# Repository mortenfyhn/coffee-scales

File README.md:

# coffee-scales

Kitchen scales, built for drip coffee brewing:

* 0.1 gram precision
* Very quick response
* Very quick tare
* Auto-starting brew timer
* Auto-off after 5 minutes

Current prototype looks something like this:

## Firmware

Setup:

1. [Install PlatformIO Core and shell commands](https://docs.platformio.org/en/latest/core/installation/index.html)
2. [Install Just](https://just.systems/man/en/packages.html)

Usage:

```sh
cd firmware
just --list
```

to list all recipes.

## Hardware

* Adafruit Feather 328P
* Load cell: 1 kg straight bar
* HX711 load cell amplifier
* Two 4-digit 7-segment displays with TM1637 drivers
* LiPo battery (1200 mAh)
* Push button for taring

## Development and debugging

Capture a log with `just log`. Then run `just replay <log>` to get the processing stages as CSV, and look at them in e.g. PlotJuggler.

Here's the state diagram:

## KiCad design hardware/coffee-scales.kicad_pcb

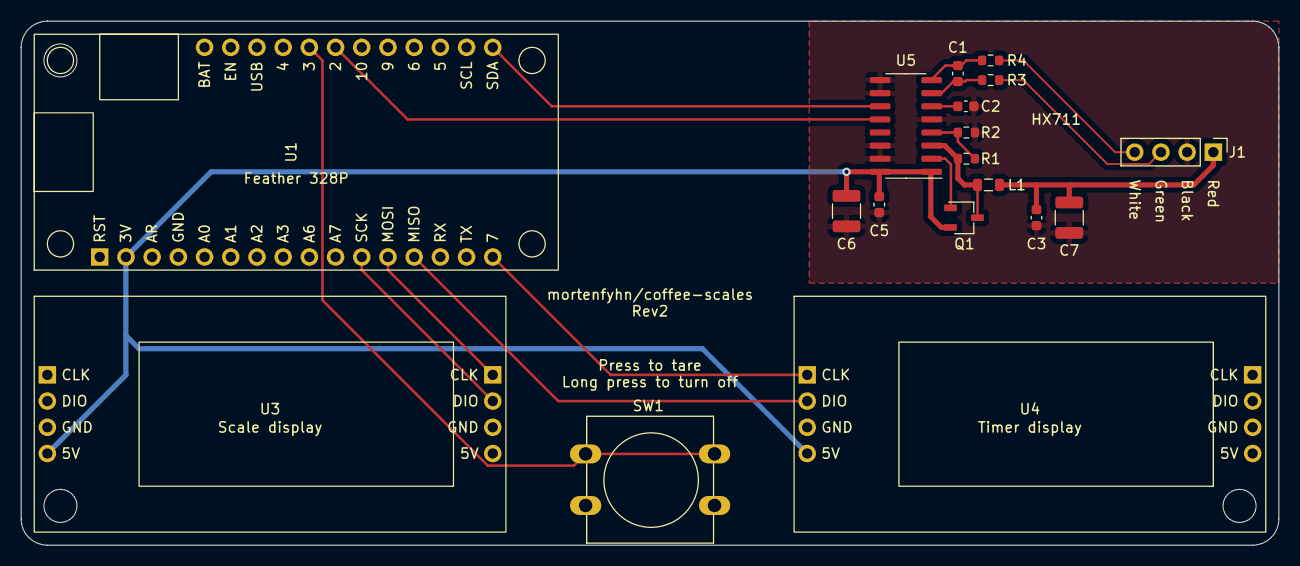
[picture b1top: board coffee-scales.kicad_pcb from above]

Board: 2 copper layers, 121.9 x 50.8 mm, 18 parts (0 on the bottom side), 18 nets.

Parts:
C1, C2, C3, C5: 0.1uF; C_0603_1608Metric
C6, C7: 10uF; C_1210_3225Metric
J1: Conn_01x04; PinHeader_1x04_P2.54mm_Vertical
L1: 3.3uH; L_0805_2012Metric
Q1: MMBT4403; TSOT-23
R1: 20k; R_0603_1608Metric
R2: 8.2k; R_0603_1608Metric
R3, R4: 100; R_0603_1608Metric
SW1: SW_Push; SW_PUSH-12mm
U1: Adafruit_Feather_328P
U3, U4: 4DIGIT_7SEG
U5: SOP-16_3.9x9.9mm_P1.27mm

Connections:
+3V3: C5.1, C6.1, Q1.2 (E), U1.2 (3V), U3.4 (5V), U4.4 (5V), U5.1 (VSUP), U5.16 (DVDD)
/HX711/A+: J1.4, R4.2
/HX711/A-: J1.3, R3.2
/HX711/DAT: U1.22 (D2), U5.12 (DOUT)
/HX711/E+: C3.1, C7.1, J1.1, L1.1
/HX711/SCK: U1.28 (SDA), U5.11 (PD_SCK)
GND: C2.1, C3.2, C5.2, C6.2, C7.2, J1.2, R2.2, SW1.2, U1.4 (GND), U3.3 (GND), U3.7 (GND), U4.3 (GND), U4.7 (GND), U5.5 (AGND), U5.9 (INNB), U5.10 (INPB), U5.14 (XI), U5.15 (RATE)
unnamed: Q1.1 (B), U5.2 (BASE)
unnamed: L1.2, Q1.3 (C), R1.1, U5.3 (AVDD)
unnamed: SW1.1, U1.21 (D3)
unnamed: U1.16 (D7), U4.1 (CLK)
unnamed: U1.13 (MISO), U4.2 (DIO)
unnamed: U1.12 (MOSI), U3.5 (CLK)
unnamed: U1.11 (SCK), U3.6 (DIO)
unnamed: C1.1, R3.1, U5.7 (INNA)
unnamed: C1.2, R4.1, U5.8 (INPA)
unnamed: C2.2, U5.6 (VBG)
unnamed: R1.2, R2.1, U5.4 (VFB)

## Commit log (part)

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2017-03-16 Add Arduino sketch
2017-08-29 Create object for gram display
2017-08-29 Create object for timer display
2017-08-29 Update pin numbers and load cell params
2017-08-29 Put opening braces on separate line
2017-08-29 Remove unnecessary filter initialization
2017-08-29 Clean up display classes
2017-09-14 Write a class for measurement filtering
2017-09-14 Tare on boot
2017-09-14 Implement hysteresis
    This reduces measurement jitter.
2017-09-14 Use member consts for smoothing filter parameters
2017-09-16 Add picture of scales to readme
2017-10-03 Remove needless functions from SmoothingFilter
2017-10-03 Take filter parameters in constructor
2017-10-03 Rename HX711 instance
2017-10-03 Un-align display instances
2017-10-03 Inherit SevenSegment classes
2017-10-03 Fix buffer size bug
    Super stupid, the extra element is needed for the decimal point.
    The _size member of RunningAverage happened to be after
    decigram_string in memory, and would get overwritten to zero,
    causing getStandardDeviation to return NAN.
2017-10-04 Update picture in readme
2017-10-04 Add support for negative weight
2017-10-10 Make static some functions that should be static
2018-07-20 Initialize platformio project
2018-07-20 Move sources to src/
2018-07-20 Rename coffee-scale.ino -> main.cpp
2018-07-20 Set monitor speed and library dependencies
2018-07-20 Add TM1637 library submodule
2018-07-20 Keep timer on
    Turns out it's really annoying that the timer resets when I remove the weight
    from the scales. Fixes #10.
2018-07-20 Set up .travis.yml
2018-07-20 Remove comment block from .travis.yml
2018-07-20 Add cool build status badge
2018-07-21 Add 500 ms delay on boot
    Fixes #11.
2018-07-21 Remove submodule stuff from travis config
2018-07-21 Add direct github link to lib_deps instead of submodule
2018-07-21 Fix constexpr warning
2019-06-01 Add build and run instructions to readme
2020-10-31 Update gitignore
2020-10-31 Update project config
2020-10-31 Update HX711 API calls
2020-11-01 Update lib README
2020-11-01 Use clang-format
2020-11-01 Remove submodule config
2020-11-01 Add Sublime Text project file
    Autogenerated from
    The current working directory /home/morten/workspace/coffee-scales will be used for the project.
    The next files/directories have been created in /home/morten/workspace/coffee-scales
    include - Put project header files here
    lib - Put here project specific (private) libraries
    src - Put project source files here
2020-11-01 Move project libs to lib/
2020-11-01 Fix warnings
2020-11-01 Setup GitHub Action
2020-11-01 Don't use SSH for dependencies
2020-11-01 Add build badge
2020-11-01 Set up scheduled build
2020-11-01 Update nightly build cron spec
    Fix #27.
2020-11-01 Refactor a bit
2020-11-01 Remove unnecessary parens
2020-11-01 Avoid printing -0.0
    Instead just print -0.1 as the first negative number.
2020-11-01 Improve tare accuracy
    Not perfect yet but better.
2020-11-02 Fix leading zero bug
    Fix #33
2020-11-08 Remove unused serial begin
2020-11-08 Add environment for Adafruit Feather 328P
2020-11-08 Support Adafruit Feather M0
2020-11-08 Readme: Numbered list
2020-11-15 Update pin connections
2020-11-15 Adjust some names
2020-11-22 Change license from MIT to GPLv3
2020-11-28 Write generic buffer lib
2020-11-28 Write Formatter lib
2020-11-28 Add printf library submodule
2020-11-28 Replace GramsDisplay
2020-11-28 Add unit testing
2020-11-28 Build with C++17
2020-11-28 Make sure negative zero prints without minus
2020-11-28 Fix CI
    Fix #38.
2020-11-29 Swap display lib
    Fix #39.
2020-11-29 Set brightness
    Fix #40
2020-11-29 Refactor with a display helper class
2020-11-29 Implement tare button
    Fix 41
2021-05-09 CI: Pin PlatformIO to v1.5.0
2021-05-09 CI: Modernize workflow
    Made it a bit closer to what the docs suggest:
    https://docs.platformio.org/en/latest//integration/ci/github-actions.html
2021-05-09 Add ItsyBitsy environment
2021-05-09 Build for ItsyBitsy
2021-05-09 CI: Use newest PlatformIO version
2021-05-09 Readme: Update build badge
2023-05-01 Revive the scales!
    I've
    * gotten everything working again on a breadboard
    * added the tare button
    * done some minor refactoring of the main file.
2023-05-01 Clean up includes and pragmas
2023-05-07 Refactor display classes
2023-05-07 Update README.md
    Fix #50
2023-05-29 Readme: Fix link to config file
2023-05-29 Support easy logging
2023-05-29 Readme: Document logging
2023-05-29 Simplify logging
2023-05-29 Add some useful logs
2023-05-29 Separate hysteresis and smoothing
2023-05-29 Refactor tare button logic
2023-05-29 Hysteresis: Rewrite to header-only
2023-05-29 Hysteresis: Make it actually work
    This makes the hysteresis work as intended...
    Makes the displayed weight a lot more stable
2023-05-29 Hysteresis: Reset when taring
    This should help with hitting exact 0.0
2023-05-30 Add log processing!
2023-05-31 Update processing script
2023-05-31 Use pin names as printed on board
2023-05-31 Add low battery warning
2023-05-31 Add some comments/grouping
2023-05-31 Clean up PlatformIO config
2023-05-31 Add startup log
2023-05-31 Rewrite process script to take command line input and output
2023-09-01 Fix low batt lamp bug
2023-09-01 Update pins
2023-09-01 Tare based on interrupt
    This makes the taring work even if you very quickly tap
    the button.
    Fix #57
2023-10-02 Update main.cpp
    This is just a test
2023-11-05 Refactor SmoothingFilter
2023-11-07 Adjust scaling for new load cell
    The old one broke
2023-12-10 Tare with averaged value
    Fix #63
2023-12-10 Specify dependency versions
2023-12-10 Use Single job starter workflow
2023-12-10 Update Semaphore config
2023-12-10 Update build badge
2023-12-10 Wait for steady state before taring
    Fix #70
2023-12-10 Reliable taring on boot, also
    Fix #32
2023-12-10 Display '----' instead of 'tArE' while taring
2023-12-10 Fix taring timer bug
2023-12-15 Implement sleep
2023-12-15 Display battery voltage at boot
2024-01-03 Disable low battery lamp
    Fix #77
2024-01-03 Display battery percentage at boot
2024-01-03 Dim display after 1 min inactivity
    Fix 76
2024-02-03 Rewrite everything as a state machine
    Fix #82
2024-02-04 Improve logging/debugging
2024-02-04 Recalibrate
2024-02-04 Cleanups
2024-02-04 Fix taring logic
    In some cases it would stay dim after taring
2024-02-04 Clarify comment
2024-05-12 Implement long press to sleep
    Fix #83
2024-12-07 Move everything to a subdir
2024-12-08 Add KiCad files
2024-12-08 Update gitignore ("auto saved files")
2024-12-08 Add a justfile
2024-12-08 Rename Sublime project file
2024-12-08 Update pin config to match PCB
2024-12-08 Clean up schematic a bit
2024-12-14 Fix some whitespace
2024-12-15 Update justfile
2024-12-23 Wire button and HX711 DT to interrupt pins
2024-12-25 Big but pointless PCB update
    * Rounded corners
    * Components not so close to the edge
    * HX711 data pin on interrupt
    * Bigger vias/pads
    * Square first pad
    * Lots of stuff added to silkscreen
2024-12-25 Move justfile up
2024-12-25 Remove unused battery header
2024-12-28 Update calibration
2024-12-28 Config pins back to current PCB
2024-12-28 Specify datatypes
2024-12-29 Optimize writing to displays
2024-12-29 Fix uncleared colon
    Workaround for this
    https://github.com/bremme/arduino-tm1637/pull/67
2024-12-29 Fix fully off when supposed to be dim
2024-12-29 Refactor brightnes logic a little
2024-12-29 Turn off red LED when sleeping
2024-12-29 Fix tests
2025-01-05 Use CI commands_file
2025-01-05 Use just for CI
2025-01-05 Add note
2025-01-05 Add (unmodified) Sparkfun HX711 breakout schematic
2025-01-05 Route most of the 328 stuff
2025-01-05 Create analog ground plane for HX711
2025-01-05 Finish HX711 integration
2025-01-05 Infinite schematic/PCB changes
2025-01-05 Integrate HX711 sub-schematic
2025-01-05 Everything routed and checked, except power supply
2025-01-06 Keep hacking
2025-10-26 Change prototype image from breadboard to PCB
    Updated image link to reflect PCB prototype.
2025-10-26 Further PCB tweaks
2025-10-26 Fix typo
2025-10-26 Rename state active -> brewing
2025-10-27 Remove old todo
2025-11-01 Update process log script
2025-11-01 Fix logging
    Fix #92
2025-11-01 Justfile: Fix path
2025-11-01 Add bias compensation to log processing
2025-11-01 Update output printing
2025-11-01 Update processing
2025-11-01 Implement anti-creep
2025-11-01 Add state diagram to readme
    Added a state diagram image to the README.
2025-11-22 Clean up logging
2025-11-22 Add CLAUDE.md
2025-11-22 Update log processing
2026-03-21 Bump CI image
2026-03-23 Unify CI recipe
